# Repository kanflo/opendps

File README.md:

# OpenDPS (p1ngb4ck fork)

#### Give your DPS5005 the upgrade it deserves

> **This is a fork of [kanflo/opendps](https://github.com/kanflo/opendps)** with firmware improvements and an accompanying ESPHome component that replaces the original ESP8266 proxy with a modern ESP32-based integration.

---

## 🙏 Special thanks

A huge, heartfelt thank you to the people without whom this project would not exist in its current form:

**[Johan Kanflo (kanflo)](https://github.com/kanflo)** — for creating OpenDPS in the first place. Reverse-engineering the DPS5005, writing a clean open-source firmware replacement, and maintaining it for years is no small feat. This fork stands entirely on his shoulders.

**[kohrar](https://github.com/kohrar)** — for creating the `dpsmode` function ([upstream PR #240](https://github.com/kanflo/opendps/pull/240)): the stock-firmware-style CV/CC interface with M1/M2 presets, power limit, timer and watt-hour meter, plus the on-device settings screen. His work is the heart of the firmware this fork ships.

**Mallow** (Discord) — for invaluable help with the LVGL UI configuration and for creating the [custom LVGL 9.5 component](https://github.com/youkorr/lvgl_9.5) that overrides ESPHome's bundled LVGL version, enabling LVGL 9.5 features on ESP32-P4. Without that work the display integration simply would not have been possible.

---

## What this fork is about

OpenDPS is awesome — so why not make the most of it? This fork pairs OpenDPS with a co-host ESP32 device to bring all of its functions together on a nice big display, with full network integration, datalogging, firmware management and plenty of room to extend further. Flash both devices once, and everything is there.

For the best experience, a **display-equipped ESP32-P4 tablet** (such as the Guition JC1060P470_I_W_Y) is recommended — but the ESPHome component works on any ESP32, including headless setups integrated into Home Assistant.

---

## Quick navigation

- [Getting started](#getting-started)
- [User manual](#user-manual)
- [Our additions](#our-additions)
- [ToDo](#todo)
- [Screenshots & feature overview](#screenshots--feature-overview)

---

## Getting started

### Step 1 — Flash the DPS with OpenDPS firmware

Follow the original project's flashing guide ([Wiki](Wiki.md) or the [upstream blog post](https://johan.kanflo.com/upgrading-your-dps5005/)) to unlock and flash your DPS device.

**Recommended:** use the firmware from this fork — it includes baud rate switching, improved ADC accuracy and calibration fixes (see [Our additions](#our-additions) below). Build and flash with:

```bash
git clone --recursive https://github.com/p1ngb4ck/opendps.git
cd opendps
make -C libopencm3
make -C dpsboot flash   # only needed for a fresh device or to update the bootloader
make -C opendps flash
```

**Already running upstream OpenDPS?** That's fine — the ESPHome component is backwards compatible with any OpenDPS version that has a working bootloader. You can always upgrade the main firmware later directly from the ESPHome device UI (no PC, no JTAG required), as long as the original `dpsboot` bootloader is intact.

> **Note:** Reflashing the bootloader (`dpsboot`) requires JTAG/SWD access. The main application firmware can be upgraded over UART by the ESPHome device at any time.

---

### Step 2 — Flash the ESPHome device

Install [ESPHome](https://esphome.io) if you haven't already, then compile and flash using our config:

```bash
# Install ESPHome (if needed)
pip install esphome

# Compile and flash (USB connected)
esphome run esphome-config/esphome_config_opendps_JC1060P470_I_W_Y.yaml
```

Or use the [ESPHome web installer](https://web.esphome.io) / [ESPHome dashboard](https://esphome.io/guides/getting_started_hassio.html) if you prefer a GUI.

The config uses `external_components` to pull the `opendps` component from this project's companion ESPHome repository — no manual component installation needed.

---

### Step 3 — Connect DPS to ESP32

Wire the DPS serial interface to your ESP32:

| DPS pin | ESP32 pin |
|---------|-----------|
| TX      | RX (see config) |
| RX      | TX (see config) |
| GND     | GND |

Exact GPIO assignments are defined in the ESPHome config file. Logic level is 3.3V on the ESP32 side — check your DPS model's serial voltage before connecting.

---

### Step 4 (optional) — Adapt the config for your hardware

The provided config targets the **Guition JC1060P470_I_W_Y** (ESP32-P4, 10.6" MIPI DSI display, IP101 Ethernet). If you use a different device:

- **Another ESP32-P4 tablet with display:** adjust display, touch and pin assignments in the YAML. Be aware that the UI currently has hardcoded sizes and positions throughout the LVGL config, so it will require manual layout adjustments to fit a different display resolution. Displays of 1024×600 or larger (e.g. 10.1") are the intended target — see the ToDo section for planned auto-sizing support.
- **Any other ESP32 (no display):** strip out the `display`, `lvgl` and `touchscreen` sections and keep only the `opendps` component with your sensors and automations. All control and monitoring works headlessly via Home Assistant or MQTT.

The `opendps` ESPHome component itself has no display dependency — the UI is purely additive.

---

### ToDo

Features planned for future implementation (not yet available):

- **UI auto-sizing** — refactor the LVGL config to derive all sizes and positions from the configured display resolution, so any display of 1024×600 or larger works without manual layout adjustments
- **BLE remote / keyboard support** — control the DPS via Bluetooth keyboard or remote
- **USB-HID support** — use a USB keyboard or gamepad connected to the ESP32 for local control
- **Minor UI fixes** — ongoing polish of the LVGL interface

---

## User manual

### Buttons and rotary encoder

The DPS front panel has four buttons (**SET**, **M1**, **M2**, **ON/OFF**) and a rotary encoder that can be turned and pressed.

| Control | Action |
|---------|--------|
| **ON/OFF** | Toggle the output on or off (settings are saved to flash when enabling) |
| **Rotary turn** | Adjust the focused value |
| **Rotary press** | Move between the digits of the focused value |
| **SET** | Focus / unfocus the selected value |
| **M1** / **M2** | Move to the previous / next value on the screen |
| **Hold SET and turn rotary** | Switch to the previous / next function screen — this is also how you reach the `settings` screen |
| **Hold M1 and press M2** | Toggle between the function screen and the calibration screen |
| **Rotary long press** | Lock / unlock the front panel |

> Recovery tip: holding **SET** while powering on forces the bootloader into firmware upgrade mode.

### Functions — how the modes actually behave

This confused us too, so read carefully: the classic OpenDPS `cv` and `cc` functions are **not** the CV/CC behavior of a typical bench supply. Their second value is a **protection cutoff**, not a limit — when it is exceeded, the output **switches off** (the screen flashes). That makes `cc` usable for battery charging with an end-of-charge voltage cutoff, but both are surprising as a general lab supply. The `cl` function is the one that behaves like a regular bench PSU.

The set of functions depends on which firmware you run — list what your device supports with `python3 dpsctl.py -d <device> -F`.

#### Firmware from this fork (dps_mode based)

The `dpsmode` function, the on-device `settings` screen and the features described below were created by [kohrar](https://github.com/kohrar) — see [upstream PR #240](https://github.com/kanflo/opendps/pull/240). All credit to him for this excellent work.

| Function | Behavior |
|----------|----------|
| `dpsmode` | Look-alike of the stock DPS firmware: set a voltage and a current limit, the hardware regulates and transitions between CV and CC (indicator icons show the active mode). A third display line cycles between an over-power protection limit (`0` = disabled), a timer and a watt-hour meter. Supports M1/M2 presets (see below). |
| `cl` | **C**urrent **L**imit — classic bench supply behavior: constant voltage until the set current is reached, then constant current. No shutdown. |
| `funcgen` | Function generator — square/saw/sine output |
| `settings` | On-device settings screen: brightness, screen update rate, calibration values, reset to defaults. Reached like any other function: hold SET and turn the rotary. |

Additional `dpsmode` controls:

| Control | Action |
|---------|--------|
| **V (M1)** / **A (M2)** | Press V (M1) to enter voltage edit, or press A (M2) to enter current edit |
| **Hold SET and press M1 or M2** | Save the current settings to preset M1 / M2 |
| **M1** / **M2** long press | Recall preset M1 / M2 (the output is switched off first) |
| **SET**, **▼ (M2)**, **SET** | To display Wh or time instead of W: press SET to enter edit mode, press the down arrow (M2) to view Wh or time, then press SET again to exit edit mode |

Available settings on the `dpsmode` third display line:

| Setting | Behavior |
|---------|----------|
| **Power limit (W)** | Over-power protection: the output is switched off if the power limit is reached. Setting it to `0.00 W` disables the limit. |
| **Wh counter** | Energy counter: the value can be adjusted, for example set back to zero. |
| **Timer** | With a value set, it is a countdown timer after which the output is switched off. When set to zero, it counts the time the output has been switched on. |

This fork's firmware also remembers the active function and restores it at power-up.

#### Upstream OpenDPS firmware (kanflo master)

| Function | Behavior |
|----------|----------|
| `cv` | Constant Voltage with over-current **cutoff**: holds the set voltage; if the output current exceeds the current setting, the output switches off. |
| `cc` | Constant Current with over-voltage **cutoff**: drives the set current; the voltage setting acts as the cutoff, e.g. the end-of-charge voltage when charging a battery. |
| `cl` | **C**urrent **L**imit — classic bench supply CV/CC behavior, as described above. |
| `funcgen` | Function generator |

---

## Our additions

### Firmware changes

- **Configurable UART baud rate** — runtime baud rate switching; default changed to 115200 for faster host communication (`b92f6de`, `31a1114`)
- **ADC oversampling** — averages 420 ADC samples per reading (~50 Hz update rate, ~21 kHz ADC rate) for significantly smoother voltage/current readings (`cdf97dd`)
- **Current noise floor clamp** — output current is clamped to zero below the 10 mA noise floor, eliminating false micro-amp readings at idle (`dc26352`)
- **ADC calibration fixes** — corrected `ADC_CHA_IOUT_GOLDEN_VALUE` for the DPS5005 and fixed double-offset bug in current averaging (`963fe78`, `bca649f`, `1f3b9ab`)
- **Vin display** — input voltage now shown with 2 decimal places (`1f3b9ab`)
- **Splash screen disabled** — faster boot (`b92f6de`)
- **dpsctl `--set-baud` / `--upgrade-baud`** — CLI support for baud rate management and baud-rate-aware firmware upgrades (`b76bc6f`)
- **dpsboot LTO + size trim** — link-time optimisation enabled in the bootloader; `hw_set_baudrate_boot` trimmed to fit in the 5 KB flash budget (`4a9a172`)
- **Status response fix** — corrected status response code handling (`e53fd42`)

### ESPHome component

The original project used a separate ESP8266 as a Wi-Fi proxy. This fork adds a **native ESPHome component** (`opendps`) that talks directly to the DPS over UART from any ESP32, replacing the proxy entirely.

**Features:**
- Real-time V_in, V_out, I_out, power and temperature sensors
- Output enable/disable, voltage/current set, function selection, lock, brightness
- OTA firmware upgrade of the DPS from USB, SD, LittleFS or network storage (NFS/SMB/FTP) — directly from the device, no PC needed
- High-speed datalogger with PSRAM-backed triple-buffering (CSV or binary output)
- Full Home Assistant integration via native API or MQTT
- Ethernet support (e.g. IP101) for wired connectivity

The component lives in the [p1ngb4ck/esphome](https://github.com/p1ngb4ck/esphome) repository under `esphome/components/opendps/`. See its [README](https://github.com/p1ngb4ck/esphome/blob/dev/esphome/components/opendps/README.md) for full documentation, configuration schema and examples.

### ESPHome configuration — Guition JC1060P470_I_W_Y (ESP32-P4 10.6" tablet)

A complete, ready-to-use ESPHome configuration for the **Guition JC1060P470_I_W_Y** is provided in [`esphome-config/esphome_config_opendps_JC1060P470_I_W_Y.yaml`](esphome-config/esphome_config_opendps_JC1060P470_I_W_Y.yaml).

**Target hardware:**
- SoC: ESP32-P4 @ 400 MHz
- Display: 10.6" MIPI DSI, 1024×600, model JC1060P470
- Touch: GT911 (I2C)
- Flash: 16 MB
- PSRAM: Octal, 200 MHz
- Ethernet: IP101

**What the config provides:**
- Full LVGL UI with main control screen (voltage, current, power, Vin, temperatures, output toggle)
- Settings page with network config, calibration editor, OTA firmware upgrade browser (USB/SD), and system info
- Datalogger integration with start/stop from the UI
- Calibration read/write with per-field numpad editing
- Ethernet connectivity (no Wi-Fi dependency)

This config is the reference implementation and is actively running on real hardware.

---

## Screenshots & feature overview

> _Screenshots and photos coming soon._

### OpenDPS supported functions

The available operating modes depend on the firmware build — see the [User manual](#user-manual) for what each function does and how the fork's function set differs from upstream. In short: `dpsmode` (stock-firmware-style CV/CC with presets), `cl` (bench supply style current limiting), `funcgen` (function generator) and `settings` on this fork; `cv`, `cc`, `cl` and `funcgen` on upstream.

**Supported devices:** DPS3003, DPS3005, DPS5005, DPS5015, DPS5020, DP50V5A and variants. Hardware revisions may vary — see the [upstream project](https://github.com/kanflo/opendps) for compatibility notes.

**Monitored values (all modes):**
- V_in — input voltage
- V_out — output voltage
- I_out — output current
- Power — calculated output power (V_out × I_out)
- Temperature 1 & 2 — internal sensors

**Control:**
- Enable / disable output
- Set voltage setpoint
- Set current limit
- Switch operating function
- Lock / unlock front panel
- Adjust display brightness
- Upgrade DPS firmware over UART (from ESP32, no PC required)
- Calibrate ADC/DAC coefficients

---

## Original project

OpenDPS is a FOSS firmware replacement for the DPS5005 (and DPS3003, DPS3005, DPS5015, DP50V5A, DPS5020 and possibly others) that has the same functionality, has a less cluttered user interface and is remote controllable via WiFi (ESP8266) or via a serial port.

There are three accompanying blog posts you might find of interest:

* [Part one](https://johan.kanflo.com/hacking-the-dps5005/) covers the reverse engineering of the DPS5005.
* [Part two](https://johan.kanflo.com/opendps-design/) describes the design of OpenDPS.
* [Part three](https://johan.kanflo.com/upgrading-your-dps5005/) covers the process of upgrading stock DPS5005:s to OpenDPS.

### Cloning & building (upstream)

```bash
git clone --recursive https://github.com/kanflo/opendps.git
cd opendps
make -C libopencm3
make -C opendps flash
make -C dpsboot flash
```

Check [the blog](https://johan.kanflo.com/upgrading-your-dps5005/) for instructions on how to unlock and flash your DPS5005.

### Setup dpsctl.py

The script requires python3 and the pyserial library:

```
pip install -r requirements.txt
```

Run it via the launcher in the repository root (`python3 dpsctl.py ...`), or install it as a command with `pip install .`. Note that `dpsctl/dpsctl.py` is part of a python package and can not be run directly.

### Usage

The functions available depend on the firmware build (see the [User manual](#user-manual)). A tool called `dpsctl.py` can be used to talk to an OpenDPS device to query functionality and supported parameters for each function (`-F` lists the functions).

Once upgraded and connected to an ESP8266, type the following at the terminal to find its IP address:

```
% dpsctl.py --scan
172.16.3.203
1 OpenDPS device found
```

Enable constant voltage (cv) at 3.3V limited to 500mA:

```
% dpsctl.py -d 172.16.3.203 -f cv
Changed function.

% dpsctl.py -d 172.16.3.203 -p voltage=3300 current=500
voltage: ok
current: ok

% dpsctl.py -d 172.16.3.203 -o on
```

Query the status of the device:

```
% dpsctl.py -d 172.16.3.203 -q
Func       : cv (on)
  current  : 500
  voltage  : 3300
V_in       : 12.35 V
V_out      : 3.33 V
I_out      : 0.152 A
```

### Upgrading DPS firmware over UART

OpenDPS comes with a bootloader enabling firmware upgrade over UART — no JTAG needed for the application firmware:

```
% make -C opendps bin
% dpsctl.py -d /dev/ttyUSB0 -U opendps/opendps_DPS5005.bin
```

(The binary is named after the `MODEL` set in the Makefile. Add `--upgrade-baud 115200` to speed the transfer up considerably.)

With this fork's ESPHome integration, firmware upgrades can be triggered directly from the ESP32 device UI or via Home Assistant — no PC or `dpsctl.py` required.

If you accidentally upgrade to a broken version, the bootloader can be forced into upgrade mode by holding the SEL button while powering on.

### Source code organisation

* `dpsboot/` — The OpenDPS bootloader
* `opendps/` — The OpenDPS firmware
* `esp8266-proxy/` — The original ESP8266 Wi-Fi proxy firmware (superseded by the ESPHome component in this fork)
* `dpsctl/` — Python script for controlling OpenDPS via Wi-Fi or serial
* `emu/` — Xcode project and GNU makefile for running an emulated OpenDPS
* `esphome-config/` — Ready-to-use ESPHome configurations for supported devices

### What about other DPS:es?

OpenDPS has been verified to work with other models in the DPSx0xx series, such as the DPS3003, DPS3005, DPS5015 and DPS5020. The maximum settable output current can be defined when building opendps, see the makefile. Please note that the hardware design might change at any time without any notice (I am not affiliated with its designer). This will render OpenDPS unusable until fixed.

---

Licensed under the MIT license. Have fun!

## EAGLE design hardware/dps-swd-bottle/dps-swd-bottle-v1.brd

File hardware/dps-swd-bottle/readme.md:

# The OpenDPS SWD Bottle

On newer DPS:es, the SWD connector is a JST-GH (1.25mm spacing that is) which translates to "really tiny". The annular rings where you need to apply solder and heat for adding wires are even smaller. This is why the OpenDPS SWD Bottle is handy. Add three P50-E2 pogo pins, and connect to your favourite SWD debugger.

## BOM

* 1x "DPS SWD BTL" PCB
* 3x P50-E2 pogo pins (about €5 for 100pcs on AliExpress)
* 1x 3 pin 0.1" male right angle header
* 3x F-F dupont cable

## Mounting

1. Add solder to each of the three exposed pads where the pogo pins will be mounted.
2. Hold one pogo pin with a tweezer or small plier an align along the pad.
3. Apply heat on the pad and when the solder reflows, gently push the pin in place and wait for the solder to cool down.
4. Repeat for the second pin and check alignment of the two pins on your DPS.
5. Repeat for the third pin and check alignment on your DPS.
6. Solder the 0.1" header *on the reverse side of the pogo pins*.

## Using

The pinout is described in the silk and you should be able to make out which is GND, SWCLK and SWDIO with a little imagination :) The DPS BTL shall be interfaced with the DPS with ground to the left, on the three rightmost rings of the SWD connector where GND is in the middle.

Soldering the right angle header on the suggested side helps you in pressing the adapter against the DPS with one hand only.

SWD *Bottle*? Well it looks like one, doesn't it?

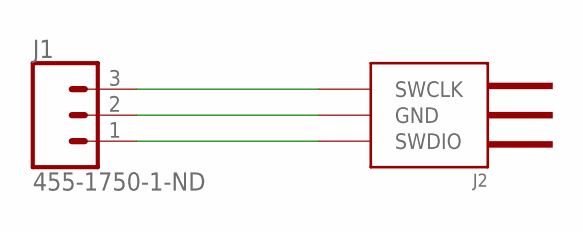
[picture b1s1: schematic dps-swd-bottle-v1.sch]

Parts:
J1: 455-1750-1-ND; 1X03
J2: DPS-SWD-PINS

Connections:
GND: J1.2, J2.GND
unnamed: J1.3, J2.SWCLK
unnamed: J1.1, J2.SWDIO

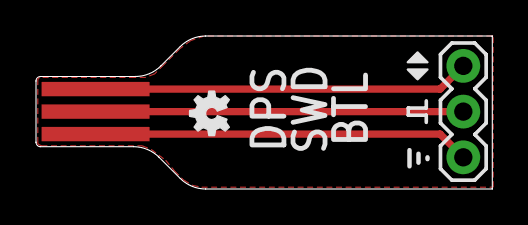
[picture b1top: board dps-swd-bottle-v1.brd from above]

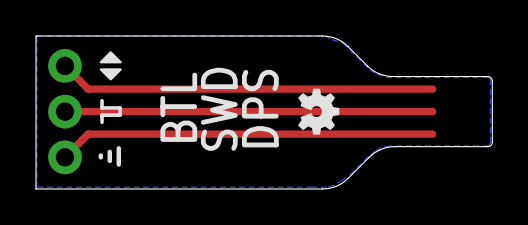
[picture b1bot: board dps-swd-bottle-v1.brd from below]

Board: 2 copper layers, 25.4 x 8.5 mm, 10 parts (4 on the bottom side), 3 nets.

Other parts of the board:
U$1, U$5: SYM-GND
U$2, U$4: SYM-DOUBLE_ARROW
U$3, U$7: SYM-CLOCK
U$6, U$8: OSHW-LOGO-MINI

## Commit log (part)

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2019-01-30 Prep for ASCII character sets.
2019-01-30 Generate 2bpp fonts, with equivalent glyph decode stage at runtime. (#116)
    * Generate 2bpp fonts, with equivalent glyph decode stage at runtime.
    * Prep for ASCII character sets.
2019-02-04 Add small bitmap font with full ascii character set. Document the 2bpp lookup table.
2019-02-06 PEP8ify the python code
2019-02-06 clarify magic number usage
2019-02-06 remove superfluous units
2019-02-08 fix missing import (#118)
2019-02-10 change constant current calibration to not use a load resistor
2019-02-10 Change constant current calibration to not use a load resistor (#122)
    * change constant current calibration to not use a load resistor
    * add thick wire requirement to calibration routine
2019-02-12 implement merged cv/cc mode
2019-02-13 implement OVP
2019-02-17 Fixed comments, removed testing frame
2019-02-17 implement merged cv/cc mode (#124)
2019-03-10 fix: compatiblity to python2 and python3 (#137)
2019-05-27 Add support for debouncing the buttons
2019-06-06 Add support for signal generator. This adds support for icon selection in the UI (the signal type: either square wave, saw, or sinus) Also fix issues with unit different than volt or ampere Convert s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
2019-09-04 Convert "Merged" to "CL" throughout the repo
2019-09-10 travis 2
2019-09-10 travis single stage
2019-09-11 mkdir -p
2019-09-11 Change default baudrate to 9600 (#156)
2019-09-12 Rename "Merged" to "Current limit" (#151)
    * Changed merged icon to "CL"
    * Convert "Merged" to "CL" throughout the repo
2019-09-13 touch model headers to rebuild
2019-09-15 fix build system
2019-09-15 added tcp comms to dspctl
2019-09-18 Force Vin_ADC, Vout_ADC and Vout_DAC through the 0,0 point
2019-09-18 Import numpy correctly in dpsctl.py
2019-09-19 import uhej only when scanning
2019-09-19 Correct speling of Python
2019-09-19 Attempting to have Travis always release binaries on master
2019-09-21 don't keep exited docker containers (#163)
2019-09-29 Added custom event handler for screens
2019-09-29 Updated large meter font size to 40px
2019-09-29 Added colored power buttons
2019-09-29 Ensure power button state is updated
2019-09-29 Fixed missing deactivated spec
2019-09-29 Added invert color feature as an option (disabled by default). Enable with INVERT_ENABLE=1 when making
2019-09-29 Removed clear code on activation because all other screens should clear on deactivation
2019-09-29 Added POWER_OFF_VISIBLE and POWER_COLORED options
2019-09-29 Added nerd font
2019-09-29 Change default build to O2
    This works for me and it makes the UI feel a little snappier (could be placebo, not sure if the UI is firmware or screen hardware limited).
    If I have a large number of local changes or custom images I find the firmware won't fit in memory with O3. I've made it O2 for now to save any future headaches from new features.
2019-09-29 Removed draw calls on enable call to prevent artifacts on next screen While the deactivate callback clears the tft display, because of uui.c's way of changing screens, another call to enable(false) i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
2019-09-30 Implemented timer, watthour meter, accessible via third row and navigation
2019-09-30 Minor bug fixes Third item will not change if in select mode Screen cannot change is locked if power is on to prevent inadvertant data/state loss Colon rendering should be less glitchy
2019-09-30 Calibrated values and they are now spot on
2019-09-30 Focus on proper item when entering select mode
2019-09-30 Keep track of third row item index
2019-09-30 Readjusted lower end amperage ADC to prevent noisy 0
2019-09-30 Added DP50V5A to readme
2019-10-01 Rework protocol handling
2019-10-01 Correct dpsboot's rx buffer size
2019-10-02 Fixed broken code
2019-10-02 Handled the new events
2019-10-02 Added M1 graphics instead of drawing something manually
2019-10-02 Added recall code
2019-10-02 Removed thermometer to save space
2019-10-02 M2 button should trigger
2019-10-02 Clear m1/m2 bar properly
2019-10-02 Power off also updates status
2019-10-02 Added brightness
2019-10-02 Added brightness to third item list
2019-10-02 Get brightness on activation
2019-10-02 Force Vin_ADC, Vout_ADC and Vout_DAC through the 0,0 point (#161)
    * Force Vin_ADC, Vout_ADC and Vout_DAC through the 0,0 point
    * Remove dead code for a copy and paste error
    * Add numpy to requirements.txt
    * Import numpy correctly in dpsctl.py
    * Convert numpy array value to float
2019-10-02 Colored power button (#167)
    * Added colored power buttons
    * Added power graphics to makefile
    Removed white power button
    * Ensure power button state is updated
    * Fixed wrong reference to on/off image size
    * Added POWER_OFF_VISIBLE and POWER_COLORED options
2019-10-02 Thermal lockout optional, default off saving 4kb flash
2019-10-02 Add make graphics option and rename logo to gfx-logo
2019-10-02 Make tick.c atomic
2019-10-04 Fixed glitchy 3rd item on start Brightness value should now be set even when screen is the first screen to start up
2019-10-04 Clear third item region when focus is changed to avoid select artifact
2019-10-04 Fixed bug with updating last time ui was drawn
2019-10-04 Pressing rot should focus on 3rd item being displayed
2019-10-04 Added brightness label
2019-10-04 Shutoff event always shuts power off Align brightness label
2019-10-04 Reset any modes on activation
2019-10-05 Makefile build should only contain dpsmode files if compiled with dpsmode Reverted some tweaks to OpenDPS defaults
2019-10-05 Fixed regression on opendps uui calls
2019-10-05 Added timer event to cause poweroff and UI updates
2019-10-05 Timer event will trigger when timer value is set to 0 Set button will leave single edit mode properly
2019-10-05 Fix invalid focus issue
2019-10-05 Added event_opp triggerd when over power protection kicks on
2019-10-06 Fixed syntax issues
2019-10-06 Adjusting layout
2019-10-06 Ensure that current_item is bound
2019-10-06 Added another row. Values should have a min/max set so it can be adjusted
2019-10-06 Added update interval
2019-10-06 Ensure that current item is in sync on activation
2019-10-06 Dividing coefficient values as floats
2019-10-06 Saving the opendps update interval to past
2019-10-06 Fixed bad reference to part_UPDATE_INTERVAL
2019-10-06 Added missing events code so it works with master Cleaned up prototype declarations
2019-10-07 Ensure that pressing rot will not enter edit mode if already in edit mode.
2019-10-08 Documentation and minor refactor
2019-10-08 Fixed opendps_screen_update_ms
2019-10-08 Make tick.c atomic (#181)
    * Make tick.c atomic
    * Replace tabs with spaces
2019-10-08 Fix 0 digit being blanked incorrectly (#185)
2019-10-10 Added min/max to fields table
2019-10-10 Added helper macros
2019-10-10 Fixed the ESP8266 proxy (#188)
2019-10-13 Fixed compile warnings in dpsmode
2019-10-13 renamed settings to ui_settings
2019-10-13 ON spacing
2019-10-13 Added field digits, decimals and unit types Added boolean to uui_c
    Squashed commit of the following:
    commit 6358c19a5a2dea07e70d289b7ef22717ece3d536
    Author: Leo Leung <leo@steamr.com>
    Date: Sun Oct 13 15:55:22 2019 -0600
    Moved enable lock down to 3rd page
    commit 0e5acfb00e023b28d53eb213e219dce102d1b2d6
2019-10-17 Ensure that digits are rendered only when in 1s place, highlighted, or meets min digit value Otherwise, blanked.
2019-10-19 Correctly unpack protocol commands
2019-10-19 Remove dead assignment
2019-10-20 Correctly unpack protocol commands (#193)
2019-10-30 Added support for DPS5020
2019-10-30 random freeze fix for DPS5015, if screen goes white when you touch multimeter probe to the GND DPS5015 connector, credits to cleverfox #419d5cb (don't know how to pull request from prev commit)
2020-03-06 Fix PyCRC installation
    The PyCRC on PyPI is incompatible with this project. I found some old clone on GitHub (mirror or fork?) providing the right version.
2020-05-28 Fixed error with raw_input(). Python3 requires input()
2020-06-21 Replaced pycrc with crc16
2020-07-12 Fix leading zero being displayed (#190)
    * Rewrote the digit drawing algorithm
    * Ensure that digits are rendered only when in 1s place, highlighted, or meets min digit value
    Otherwise, blanked.
    * Signed power value
2021-02-13 make build_binaries macOS compatible
2021-02-14 flashing srecs means bootloader isn't overwritten by opendps
2021-02-14 Added DPS3003 default parameters and fixed overflow in pwrctl_calc_ilimit_adc. (#226)
    The calibration of DPS3003 often resulted in malfunctioning of
    CC and CL function due to a bug in pwrctl.c:pwrctl_calc_ilimit_adc:
    The float value in pwrctl_calc_ilimit_adc might result in overflow
    during the casting to the return value of type uint16_t.
    The return type is changed to uint32_t.
2021-02-15 fix for sourcecode include (#192)
2021-02-21 move wdog_init to right before the event handler loop
2021-02-22 CV_ENABLE by default on
2021-02-22 CC enabled by default too
2021-03-14 give reset a little time
2021-03-14 Watchdog (#233)
    * .gitignore vim swap files
    * simple watchdog implementation
    * move wdog_init to right before the event handler loop
    * add instrumentation code for wdog
    * give ili9163c reset a little time
    * WDOG as makefile option
2021-05-22 Settings screen now uses the gear icon
2021-05-22 Refined UI rendering to avoid redrawing elements unnecessarily.
    The UI was excessively redrawn when screens change with the call to
    uui_refresh. This causes UI elements to flicker. Instead, each screen
    will need to refresh only what is necessary on activation
    The settings screen no longer flicker when moving through pages as only
    the table portion is blanked with a tft_fill call rather than tft_clear.
2021-05-23 DPS screen will only save presets and last settings when necessary
    A bunch of events were triggeringg past_save. This change will only
    trigger a write when power is turned on or when presets are saved to
    reduce flash wear.
2021-05-24 Fixed incorrect past save IDs in DPS mode.
    This issue resulted in recalls failing after a reset.
2021-05-25 Reduce jitter in ADC values / readings.
    Apply oversampling to the ADC values to reduce jitter (OVP / OCP) and LCD readings.
2021-05-25 Fix assert code in CONFIG_RELEASE mode.
2021-05-25 Add MPPT support / screen.
    Be careful with this!
    This screen automatically enables the output (so it starts when the solar panel generates power).
    It uses a binary tree search to quickly find the maximum power point of the input source.
    The output is limited to the voltage / current limits set on the screen.
2021-05-26 Update calibration values for DPS5020
2021-06-04 Added a low input voltage warning
    If insufficient voltage is provided for the set voltage, a warning bar
    will be displayed next to the voltage value. This will override the
    constant voltage / constant current mode as it stops functioning
    properly in this state.
2021-06-10 Corrected incorrect C/K Vin setting labels
2022-06-14 Update dps-model.h
    LINE 25 * K = (U1-U2)/(ADC1-ADC2) = (18000-5001)/(1393-394) = 13.01201201 (UPDATE CALC RESULT)
2023-04-08 bootloader fix
    Revert to deprecated rcc_clock_setup_in_hsi_out_48mhz in order to fit
    within the 5K limit.
    Disable link time optimization
2025-05-24 opendps/uframe: check for overflow
    Instead of calling `memcpy` with a too large payload, bail out and
    report the error when the received uframe is too large.
2025-05-24 dpsctl: update to python3
    - use python3 instead of python in the shebang
    - replace dependency to crc16 with the implementation already in use
    in the uframe module
2025-05-25 dpsctl: update to python3 (#264)
    - use python3 instead of python in the shebang
    - replace dependency to crc16 with the implementation already in use
    in the uframe module
2025-06-29 feat(protocol): Add input validation for voltage and current setpoints
    Incoming setpoint commands for voltage and current from the host were not
    validated before being used by the power control module.
    This created a safety risk where a malformed or out-of-range value could be
    written directly to the hardware DACs. This could result in an output
    voltage/current that exceeds the device's safe operating area, potentially
    damaging the OpenDPS unit or the connected load.
2026-01-26 add latest esphome related changes
2026-02-03 fix status response code
2026-02-14 Fix SPI initialization for libopencm3 update (#268)
    Replace rcc_periph_reset_pulse() with explicit hold/release sequence
    to restore display functionality after libopencm3 update.
    Fixes black screen issue on DPS5015 after recent libopencm3 changes.
2026-02-15 feat(safety): Add bounds checking for voltage, current and calibration values
    Adds validation to prevent out-of-range values from being written to hardware
    or stored as calibration coefficients.
    Changes:
    - pwrctl.c: Add sanity limits (65V max input, 60V max output, 20A max current)
    - opendps.c: Validate calibration coefficients with reasonable bounds
    Invalid values are rejected, maintaining the last valid state.

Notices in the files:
parts and their libraries:
SparkFun-Connectors: Licensing: Creative Commons ShareAlike 4.0 International - https://creativecommons.org/licenses/by-sa/4.0
